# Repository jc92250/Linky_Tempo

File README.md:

# Linky_Tempo
Délestage fil pilote

L'objectif de ce petit montage est de délester mon chauffage électrique (via ses fils pilote):
- en période HPJR (heure pleine jour rouge)
- en période HPJW (heure pleine jour blanc) avec possibilité d'annuler le délestage
- en cas de surconsommation

L'arduino est connecté à la sortie TIC (télé-information client) du compteur Linky.
Le compteur doit être configuré en mode "Historique" (c'est son mode par défaut)
Parmi les informations reçues, on s'intéresse:
- à la période en cours de l'abonnement Tempo
- à la consommation instantanée

Lorsque la période en cours est HPJR (heure pleine jour rouge), l'Arduino envoie un signal de délestage aux fils pilote des radiateurs.
Durant cette période, il n'y a aucun moyen d'annuler ce délestage.

Lorsque la période en cours est HPJW (heure pleine jour blanc), l'Arduino envoie également un signal de délestage aux fils pilote des radiateurs.
Durant cette période, il est possible d'annuler le délestage via un appui sur le bouton poussoir.
Le délestage est alors annulé jusqu'à la fin de la période HPJW (typiquement, dès que le compteur passe en heure creuse)
Un second appui sur le bouton poussoir réactive le délestage.
Ce bouton poussoir n'a d'effet qu'en période HPJW.

Par ailleurs, le délestage peut également être activé lors d'une surconsomation (typiquement, si un four et des plaques électriques sont allumés alors que le chauffage est par ailleur activé)
Ce délestage intervient dès que la consommation électrique instantanée atteint 80% de la puissance souscrite.

Lorsque le délestage est activé, il dure au minimum 4mn (pour tenir compte de l'aspect intermittent de la consommation électrique d'un four ou d'une plaque électrique)

Le fichier config.h définit les paramètres dont les valeurs peuvent être ajustées.

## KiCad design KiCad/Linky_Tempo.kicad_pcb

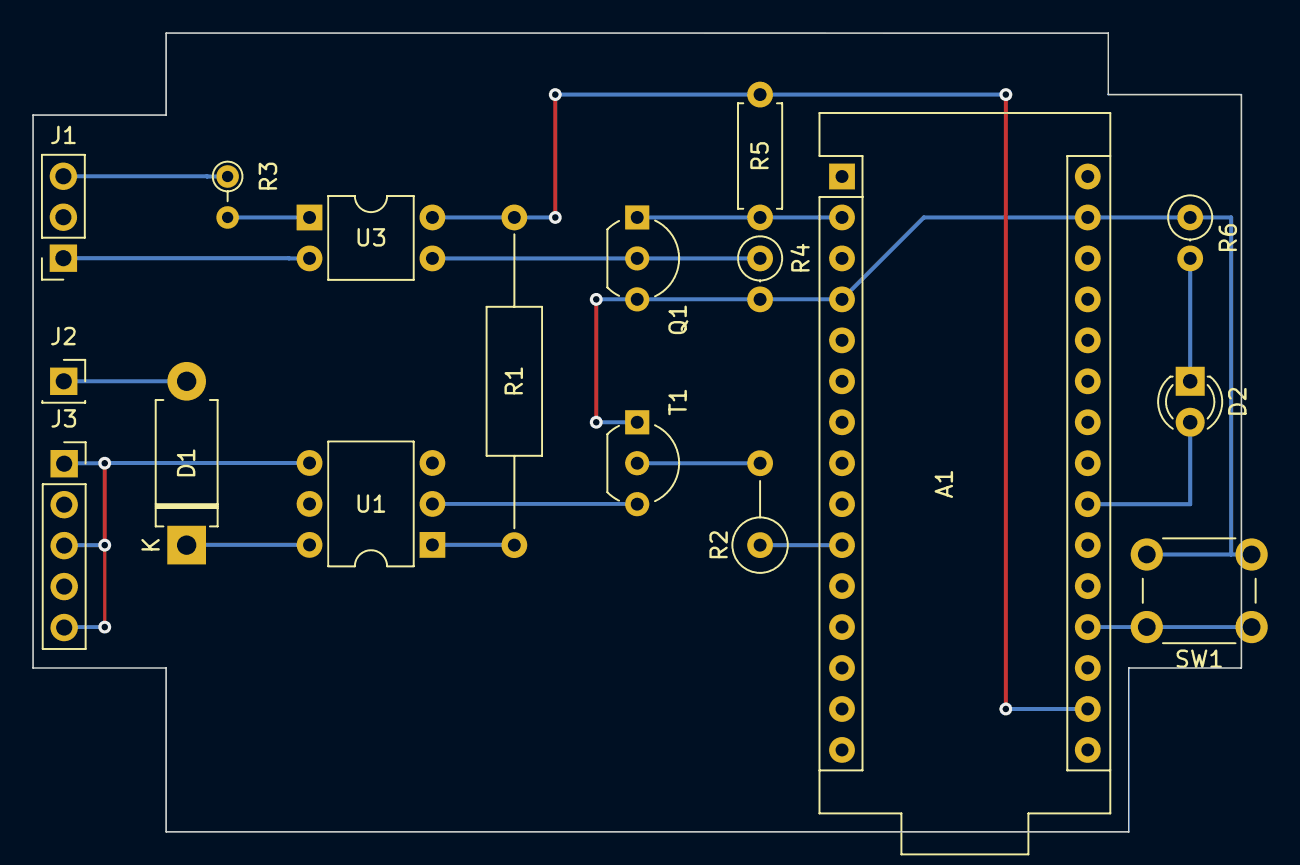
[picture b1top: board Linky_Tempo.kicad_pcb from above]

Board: 2 copper layers, 74.9 x 49.5 mm, 17 parts (0 on the bottom side), 15 nets.

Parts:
A1: Arduino_Nano_Socket; Arduino_Nano
D1: 1N4007; D_DO-15_P10.16mm_Horizontal
D2: LED; LED_D3.0mm
J1: TIC; PinSocket_1x03_P2.54mm_Vertical
J2: Main; PinSocket_1x01_P2.54mm_Vertical
J3: FP; PinSocket_1x05_P2.54mm_Vertical
Q1: BS170; TO-92_Inline_Wide
R1: 110Ω; R_Axial_DIN0309_L9.0mm_D3.2mm_P20.32mm_Horizontal
R2: 1.5kΩ; R_Axial_DIN0309_L9.0mm_D3.2mm_P5.08mm_Vertical
R3: 2,2kΩ; R_Axial_DIN0204_L3.6mm_D1.6mm_P2.54mm_Vertical
R4: 10kΩ; R_Axial_DIN0207_L6.3mm_D2.5mm_P2.54mm_Vertical
R5: 10kΩ; R_Axial_DIN0207_L6.3mm_D2.5mm_P7.62mm_Horizontal
R6: 1kΩ; R_Axial_DIN0207_L6.3mm_D2.5mm_P2.54mm_Vertical
SW1: SW_Push; SW_PUSH_6mm
T1: 2N2222; TO-92_Inline_Wide
U1: MOC3041M; DIP-6_W7.62mm
U3: LTV-814; DIP-4_W7.62mm

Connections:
+3V3: A1.17 (3V3), R1.1, R5.1, U3.4
/I1: J1.1, U3.2
/I2: J1.3, R3.1
Earth: A1.4 (GND), A1.29 (GND), Q1.3 (S), R4.2, R6.1, SW1.2, T1.1 (E)
unnamed: A1.2 (D0/RX), Q1.1 (D), R5.2
unnamed: A1.10 (D7), R2.1
unnamed: D1.2 (A), J2.1
unnamed: D1.1 (K), U1.6
unnamed: D2.1 (K), R6.2
unnamed: J3.1, J3.3, J3.5, U1.4
unnamed: Q1.2 (G), R4.1, U3.3
unnamed: R1.2, U1.1
unnamed: R3.2, U3.1
unnamed: R2.2, T1.2 (B)
unnamed: T1.3 (C), U1.2

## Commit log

2024-12-21 Ajout de fichiers locaux
2024-12-21 description
2025-01-05 typo
